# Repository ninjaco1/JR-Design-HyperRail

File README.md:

# JR-Design-HyperRail
Hyper Rail Group 7

By: Anthony Nguyen, Triet Nguyen, Ben Chan

## System Testing Videos 
Currently don't have at the moment: 
[System Testing Video]()

## Artifacts
PDF for the project summary: 
[Project Summary](https://docs.google.com/document/d/1FK-zv3ej4hmk3cCyDUM1-cvGXo1tJJXo0p-roIx5XGc/edit?usp=sharing)

Steps on how to this project runs: 
[Developer Guide](https://drive.google.com/file/d/1b8bf6LgNn7jMLtsA6zKb3VHLeMdlCe0p/view?usp=sharing)

[Design Presentation Slides](https://docs.google.com/presentation/d/1P-iVZDowQR9feOQwt1mziY3U6oYqxVLCjaJKAJ0mzws/edit?usp=sharing)

[Design Presentation Video](https://drive.google.com/file/d/1qnwT8EZ-0XLxV4VDlUW8I-kmaopJeuQv/view?usp=sharing)

[Top-Level Block Diagram](https://drive.google.com/file/d/1eomTYj-uaLoGJ_eJbNjmGpFzPQzX-4X2/view?usp=sharing)

[Time report showing time spent by each team member](https://docs.google.com/spreadsheets/d/1bjDdPKETd7_wlSsTo6gn0jvfjcJVhAvTHsii9ZCNzQg/edit?usp=sharing)

## Demo Videos with Explanation 
First change Directories so that you are in the `EdgeDetection` directory. Before running the python script change code on line 5 to 
```python 
img = cv2.imread('path/to/image.png',0)
```
. Make sure to update the file path to the image that you wish to perform edge detection on. Afterwards run `python3 edgeDetection.py`. At the end it will show the edge detection picture compared to the original one which was in gray, and a generated G-Code command text file called `gcode.txt`.
[Edge Detection Demo in Python3](https://drive.google.com/file/d/1J3HoQEe9SpAp14uiTM5HVKii-mfcHyuJ/view?usp=sharing)

To run this file make sure you are using some type of Python Interpreter otherwise it will not work. Change directory to `Parser`. To run the script run `python3 parser.py`. Then it will ask if you want to to run in manual mode or auto mode.
1. Auto Mode: provide the G-Code text file.
2. Manual Mode: Type G-Code commands one at a time

The G-Code commands must have the right parameters/arguments plus the command or it will not run. Ex: `G0 X0 Y0` would be 3 total.

1 total: G20, G21, G90, G91, M2, M6, M72, T#

3 total: G0

4 total: G1

6 total: G3

[G-Code Parser in Python3 Demo Video](https://drive.google.com/file/d/1lWumYBpXrusXX2kpaQBLoHpFK_WG9Xnz/view?usp=sharing)

[G-Code Parser in MATLAB Demo Video](https://drive.google.com/file/d/1U7hCthpk_3eQoVkrieUcnGUcYebdRAjs/view?usp=sharing)

## Picture of PCB and Toolhead 

[Google Drive folder with images of PCB layers and toolhead](https://drive.google.com/drive/folders/1xzrkDD5itXDCg26j8iZeH8htb0uEpJzJ?usp=sharing)

## Bill of Materials 

[BOM](https://drive.google.com/file/d/1bA2rW0vcZreU9mbd2lWcmnBElYSLbTTa/view?usp=sharing)

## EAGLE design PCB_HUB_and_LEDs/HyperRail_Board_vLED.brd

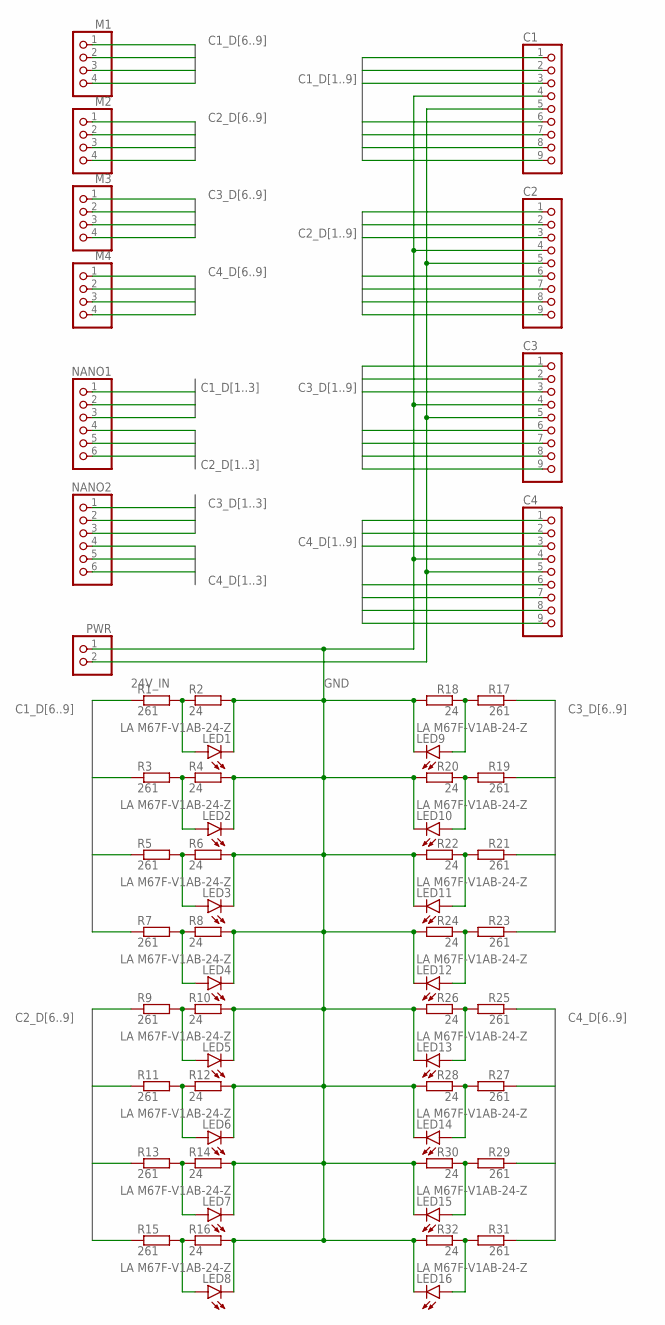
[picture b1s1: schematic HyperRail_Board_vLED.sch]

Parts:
C1, C2, C3, C4: PINHD-1X9; 1X09
LED1, LED2, LED3, LED4, LED5, LED6, LED7, LED8, LED9, LED10, LED11, LED12, LED13, LED14, LED15, LED16: LA M67F-V1AB-24-Z; PLCC2
M1, M2, M3, M4: PINHD-1X4; 1X04
NANO1, NANO2: PINHD-1X6; 1X06
PWR: PINHD-1X2; 1X02
R1, R3, R5, R7, R9, R11, R13, R15, R17, R19, R21, R23, R25, R27, R29, R31: 261; SMK
R2, R4, R6, R8, R10, R12, R14, R16, R18, R20, R22, R24, R26, R28, R30, R32: 24; SMK

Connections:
24V_IN: C1.5, C2.5, C3.5, C4.5, PWR.2
C1_D1: C1.1, NANO1.1
C1_D2: C1.2, NANO1.2
C1_D3: C1.3, NANO1.3
C1_D6: C1.6, M1.1, R1.2
C1_D7: C1.7, M1.2, R3.2
C1_D8: C1.8, M1.3, R5.2
C1_D9: C1.9, M1.4, R7.2
C2_D1: C2.1, NANO1.4
C2_D2: C2.2, NANO1.5
C2_D3: C2.3, NANO1.6
C2_D6: C2.6, M2.1, R9.2
C2_D7: C2.7, M2.2, R11.2
C2_D8: C2.8, M2.3, R13.2
C2_D9: C2.9, M2.4, R15.2
C3_D1: C3.1, NANO2.1
C3_D2: C3.2, NANO2.2
C3_D3: C3.3, NANO2.3
C3_D6: C3.6, M3.1, R17.2
C3_D7: C3.7, M3.2, R19.2
C3_D8: C3.8, M3.3, R21.2
C3_D9: C3.9, M3.4, R23.2
C4_D1: C4.1, NANO2.4
C4_D2: C4.2, NANO2.5
C4_D3: C4.3, NANO2.6
C4_D6: C4.6, M4.1, R25.2
C4_D7: C4.7, M4.2, R27.2
C4_D8: C4.8, M4.3, R29.2
C4_D9: C4.9, M4.4, R31.2
GND: C1.4, C2.4, C3.4, C4.4, LED1.C, LED2.C, LED3.C, LED4.C, LED5.C, LED6.C, LED7.C, LED8.C, LED9.C, LED10.C, LED11.C, LED12.C, LED13.C, LED14.C, LED15.C, LED16.C, PWR.1, R2.1, R4.1, R6.1, R8.1, R10.1, R12.1, R14.1, R16.1, R18.1, R20.1, R22.1, R24.1, R26.1, R28.1, R30.1, R32.1
unnamed: LED1.A, R1.1, R2.2
unnamed: LED2.A, R3.1, R4.2
unnamed: LED3.A, R5.1, R6.2
unnamed: LED4.A, R7.1, R8.2
unnamed: LED5.A, R9.1, R10.2
unnamed: LED6.A, R11.1, R12.2
unnamed: LED7.A, R13.1, R14.2
unnamed: LED8.A, R15.1, R16.2
unnamed: LED9.A, R17.1, R18.2
unnamed: LED10.A, R19.1, R20.2
unnamed: LED11.A, R21.1, R22.2
unnamed: LED12.A, R23.1, R24.2
unnamed: LED13.A, R25.1, R26.2
unnamed: LED14.A, R27.1, R28.2
unnamed: LED15.A, R29.1, R30.2
unnamed: LED16.A, R31.1, R32.2

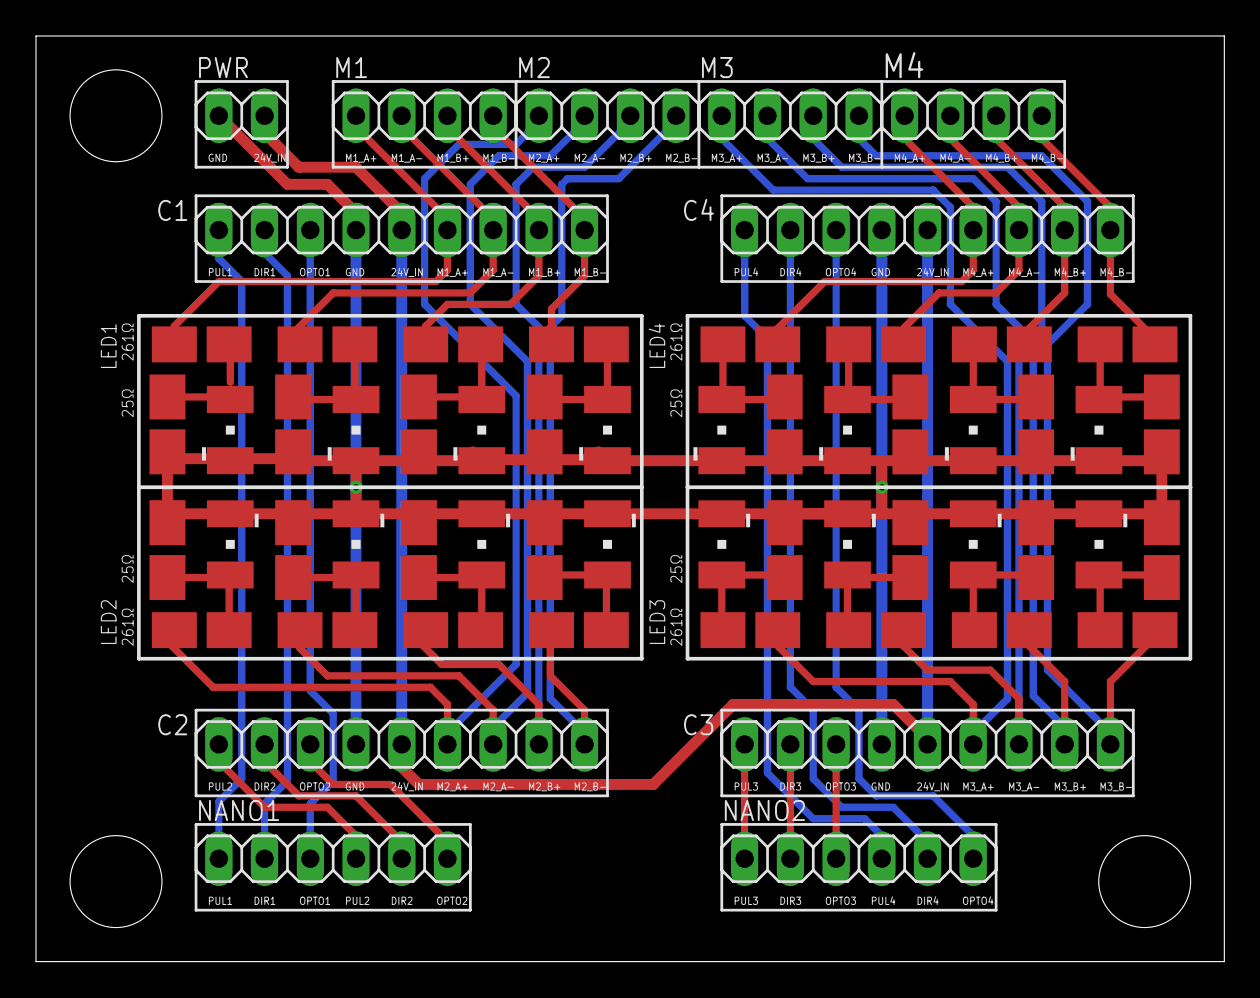
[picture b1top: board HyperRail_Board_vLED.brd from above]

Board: 2 copper layers, 66.0 x 51.4 mm, 59 parts (0 on the bottom side), 46 nets.

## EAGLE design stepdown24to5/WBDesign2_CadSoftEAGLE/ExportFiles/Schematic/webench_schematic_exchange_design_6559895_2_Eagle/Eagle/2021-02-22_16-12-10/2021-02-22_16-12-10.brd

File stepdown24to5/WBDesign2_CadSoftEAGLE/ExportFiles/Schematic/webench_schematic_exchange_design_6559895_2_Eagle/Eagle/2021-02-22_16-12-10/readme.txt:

**********************************************************
*************  Important Instructions Follow  ************
**********************************************************
 
All files exported to: Z:\\65\\59\\6559895\\2\Eagle\2021-02-22_16-12-10\2021-02-22_16-12-10.xml

**********************************************************
*****************Schematic Instructions  *******************
**********************************************************

To import your new Schematic file into Eagle:

1. Unzip the downloaded folder files to local directory and Start Eagle.
2. Select "File"->"Open"->"Schematic..." from the menu at the top of
the screen.
3. Browse to your newly exported file and select the ".sch" file extension.
4. You should now see your schamtic available in Eagle.

**********************************************************
*******************  PCB Instructions  *******************
**********************************************************

To import your new BOARD file into Eagle:

1. Unzip the downloaded folder files to local directory and Start Eagle.
2. Select "File"->"Open"->"Board..." from the menu at the top of
the screen.
3. Browse to your newly exported file and select the ".brd" file extension.
4. Planes will need to be repoured to update the polygon fills
	1. Once your board is loaded, type "ratsnest" into the command
	   line and press the Enter key.
	2. The polygons should all be filled now.
5. You should now have an image of your board available in Eagle.

**********************************************************
*******************  LIB Instructions  *******************
**********************************************************

To import your new library into Eagle:

1. Start Eagle.
2. Select "File"->"New"->"Library" from the menu.
3. In the blank library window, select "File" -> "Execute Script"
from the menu.
5. Browse to your newly exported Eagle Script file (".scr" file extension)
6. After opening the file, the script will populate the new library.
Layer 93 should NOT exist.
7. Use "File"->Save As: "AcceleratedDesigns_Lib.lbr" and to the desired
location in Eagle native format.
8. Update schematic with the imported library, Select Library and click on Update; open the library file
	and sync. each part.

For additional information, please visit this site:
http://www.accelerated-designs.com/help/Eagle_import.html

You may also find this video helpful:
http://youtu.be/5jGuWY-Yy3Q

**********************************************************
**********************************************************
**********************************************************

Component "C1608X5R1A226M080AC" renamed to "C1608X5R1A226M080AC"
Component "CRCW04022M00FKED" renamed to "CRCW04022M00FKED"
Component "CRCW0402383KFKED" renamed to "CRCW0402383KFKED"
Component "WB_GND" renamed to "WB_GND"
Component "CRCW0402100KFKED" renamed to "CRCW0402100KFKED"
Component "NPI54C100MTRF" renamed to "NPI54C100MTRF"
Component "GRM21BR71E225KA73L" renamed to "GRM21BR71E225KA73L"
Component "TPS62175DQCR" renamed to "TPS62175DQCR"
Component "WB_BATTERY" renamed to "WB_BATTERY"
Component "WB_CURRENT_LOAD" renamed to "WB_CURRENT_LOAD"
The Symbol WB_CONTINUATION was missing a RefDes attribute, a refdes was created for the symbol.
The Symbol WB_CONTINUATION was missing a Type attribute, a type was created for the symbol.
The Symbol WB_CONTINUATION was missing a Value attribute, a value was created for the symbol.
The Symbol WB_BLOCK_IO was missing a RefDes attribute, a refdes was created for the symbol.
The Symbol WB_BLOCK_IO was missing a Type attribute, a type was created for the symbol.
The Symbol WB_BLOCK_IO was missing a Value attribute, a value was created for the symbol.
The Symbol WB_PWL_VOLTAGE_SOURCE was missing a RefDes attribute, a refdes was created for the symbol.
The Symbol WB_PWL_VOLTAGE_SOURCE was missing a Type attribute, a type was created for the symbol.
The Symbol WB_PWL_VOLTAGE_SOURCE was missing a Value attribute, a value was created for the symbol.
The Symbol WB_SOURCE_RESISTOR was missing a RefDes attribute, a refdes was created for the symbol.
The Symbol WB_SOURCE_RESISTOR was missing a Type attribute, a type was created for the symbol.
The Symbol WB_SOURCE_RESISTOR was missing a Value attribute, a value was created for the symbol.
The Symbol WB_PRIM_PWL_VOLTAGE_SOURCE was missing a RefDes attribute, a refdes was created for the symbol.
The Symbol WB_PRIM_PWL_VOLTAGE_SOURCE was missing a Type attribute, a type was created for the symbol.
The Symbol WB_PRIM_PWL_VOLTAGE_SOURCE was missing a Value attribute, a value was created for the symbol.
The Symbol WB_CURRENT_PROBE was missing a RefDes attribute, a refdes was created for the symbol.
The Symbol WB_CURRENT_PROBE was missing a Type attribute, a type was created for the symbol.
The Symbol WB_CURRENT_PROBE was missing a Value attribute, a value was created for the symbol.
The Symbol WB_LOAD_RESISTOR was missing a RefDes attribute, a refdes was created for the symbol.
The Symbol WB_LOAD_RESISTOR was missing a Type attribute, a type was created for the symbol.
The Symbol WB_LOAD_RESISTOR was missing a Value attribute, a value was created for the symbol.
The Symbol WB_PRIM_STARTUP_VOLTAGE_SOURCE was missing a RefDes attribute, a refdes was created for the symbol.
The Symbol WB_PRIM_STARTUP_VOLTAGE_SOURCE was missing a Type attribute, a type was created for the symbol.
The Symbol WB_PRIM_STARTUP_VOLTAGE_SOURCE was missing a Value attribute, a value was created for the symbol.
The Symbol WB_STARTUP_VOLTAGE_SOURCE was missing a RefDes attribute, a refdes was created for the symbol.
The Symbol WB_STARTUP_VOLTAGE_SOURCE was missing a Type attribute, a type was created for the symbol.
The Symbol WB_STARTUP_VOLTAGE_SOURCE was missing a Value attribute, a value was created for the symbol.
The Symbol WB_PWL_CURRENT_LOAD was missing a RefDes attribute, a refdes was created for the symbol.
The Symbol WB_PWL_CURRENT_LOAD was missing a Type attribute, a type was created for the symbol.
The Symbol WB_PWL_CURRENT_LOAD was missing a Value attribute, a value was created for the symbol.
The Symbol WB_PRIMITIVE_BATTERY was missing a RefDes attribute, a refdes was created for the symbol.
The Symbol WB_PRIMITIVE_BATTERY was missing a Type attribute, a type was created for the symbol.
The Symbol WB_PRIMITIVE_BATTERY was missing a Value attribute, a value was created for the symbol.
The Symbol WB_VOLTAGE_PROBE was missing a RefDes attribute, a refdes was created for the symbol.
The Symbol WB_VOLTAGE_PROBE was missing a Type attribute, a type was created for the symbol.
The Symbol WB_VOLTAGE_PROBE was missing a Value attribute, a value was created for the symbol.
The Symbol WB_TPS62175DQC was missing a RefDes attribute, a refdes was created for the symbol.
The Symbol WB_TPS62175DQC was missing a Type attribute, a type was created for the symbol.
The Symbol WB_TPS62175DQC was missing a Value attribute, a value was created for the symbol.

Ultra Librarian Gold 8.1.204 Process Report

Message - Padstack "RX26Y38D0T" Shape(4) is a CIRCLE with no diameter.
Message - Padstack "RX22Y24D0T" Shape(4) is a CIRCLE with no diameter.
Message - Padstack "RX84p5Y217D0T" Shape(4) is a CIRCLE with no diameter.
Message - Padstack "RX44Y57D0T" Shape(4) is a CIRCLE with no diameter.
Message - Padstack "R10100200000200A" Shape(4) is a CIRCLE with no diameter.
Message - Padstack "R10330940000217A" Shape(4) is a CIRCLE with no diameter.
Message - Pattern "IND_NPI54C", entity (115-Line) is a LINE with matching start and end points.
Message - Pattern "IND_NPI54C", entity (117-Line) is a LINE with matching start and end points.
Message - Pattern "IND_NPI54C", entity (119-Line) is a LINE with matching start and end points.
Message - Pattern "IND_NPI54C", entity (121-Line) is a LINE with matching start and end points.
Message - Symbol "WB_CAPACITOR" has as multiple attributes named "TYPE".
One of the attributes was renamed to "TYPE_2".
Message - Component "C1608X5R1A226M080AC" attribute "Datasheet URL" references text style "" that is not in the database.
The default pattern text style "H50s3" was substituted.
Message - Component "C1608X5R1A226M080AC" attribute "Cap" references text style "" that is not in the database.
The default pattern text style "H50s3" was substituted.
Message - Component "C1608X5R1A226M080AC" attribute "ESR" references text style "" that is not in the database.
The default pattern text style "H50s3" was substituted.
Message - Component "C1608X5R1A226M080AC" attribute "IRMS" references text style "" that is not in the database.
The default pattern text style "H50s3" was substituted.
Message - Component "C1608X5R1A226M080AC" attribute "VDC" references text style "" that is not in the database.
The default pattern text style "H50s3" was substituted.
Message - Component "CRCW04022M00FKED" attribute "Resistance" references text style "" that is not in the database.
The default pattern text style "H50s3" was substituted.
Message - Component "CRCW04022M00FKED" attribute "Power" references text style "" that is not in the database.
The default pattern text style "H50s3" was substituted.
Message - Component "CRCW04022M00FKED" attribute "Tolerance" references text style "" that is not in the database.
The default pattern text style "H50s3" was substituted.
Message - Component "CRCW0402383KFKED" attribute "Resistance" references text style "" that is not in the database.
The default pattern text style "H50s3" was substituted.
Message - Component "CRCW0402383KFKED" attribute "Power" references text style "" that is not in the database.
The default pattern text style "H50s3" was substituted.
Message - Component "CRCW0402383KFKED" attribute "Tolerance" references text style "" that is not in the database.
The default pattern text style "H50s3" was substituted.
Message - Component "CRCW0402100KFKED" attribute "Resistance" references text style "" that is not in the database.
The default pattern text style "H50s3" was substituted.
Message - Component "CRCW0402100KFKED" attribute "Power" references text style "" that is not in the database.
The default pattern text style "H50s3" was substituted.
Message - Component "CRCW0402100KFKED" attribute "Tolerance" references text style "" that is not in the database.
The default pattern text style "H50s3" was substituted.
Message - Component "NPI54C100MTRF" attribute "L" references text style "" that is not in the database.
The default pattern text style "H50s3" was substituted.
Message - Component "NPI54C100MTRF" attribute "DCR" references text style "" that is not in the database.
The default pattern text style "H50s3" was substituted.
Message - Component "NPI54C100MTRF" attribute "IDC" references text style "" that is not in the database.
The default pattern text style "H50s3" was substituted.
Message - Component "GRM21BR71E225KA73L" attribute "Cap" references text style "" that is not in the database.
The default pattern text style "H50s3" was substituted.
Message - Component "GRM21BR71E225KA73L" attribute "ESR" references text style "" that is not in the database.
The default pattern text style "H50s3" was substituted.
Message - Component "GRM21BR71E225KA73L" attribute "IRMS" references text style "" that is not in the database.
The default pattern text style "H50s3" was substituted.
Message - Component "GRM21BR71E225KA73L" attribute "VDC" references text style "" that is not in the database.
The default pattern text style "H50s3" was substituted.

TextStyle count:  24
Padstack count:   6
Pattern count:    5
Symbol count:     20
Component count:  10

Export

Footprint "WB_GND" has no layer data mapped and will be skipped.
Component "WB_GND" requires footprint "WB_GND" and will be skipped.
Footprint "WB_BATTERY" has no layer data mapped and will be skipped.
Component "WB_BATTERY" requires footprint "WB_BATTERY" and will be skipped.
Footprint "WB_CURRENT_LOAD" has no layer data mapped and will be skipped.
Component "WB_CURRENT_LOAD" requires footprint "WB_CURRENT_LOAD" and will be skipped.

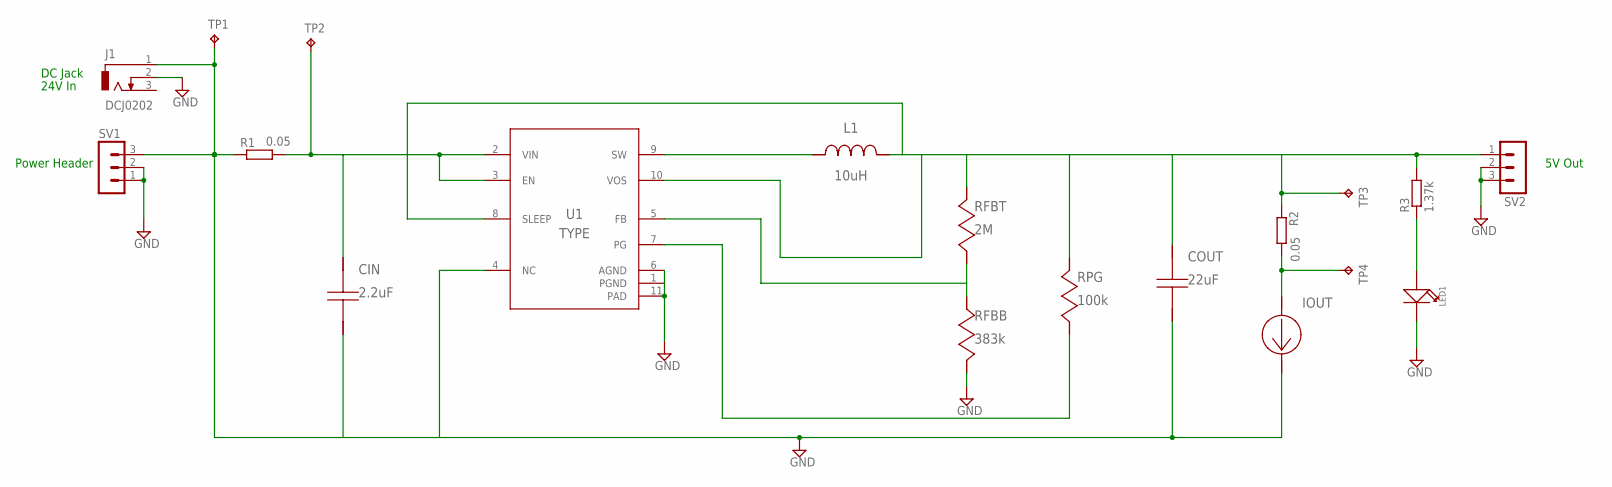
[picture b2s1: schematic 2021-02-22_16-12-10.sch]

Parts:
CIN: 2.2uF; 0805
COUT: 22uF; 0603
IOUT: WB_CURRENT_LOAD
J1: DCJ0202
L1: 10uH; IND_NPI54C
LED1: LED-THT
R1, R2: 0.05; R0603
R3: 1.37k; R0603
RFBB: 383k; 0402
RFBT: 2M; 0402
RPG: 100k; 0402
SV1, SV2: MA03-1
TP1, TP2, TP3, TP4: TPPAD1-20; P1-20
U1: TPS62175DQCR; DQC0010A

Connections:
1: RPG.2, U1.7 (PG)
2: COUT.1, RFBT.1, RPG.1, U1.8 (SLEEP), U1.10 (VOS)
3: L1.1, U1.9 (SW)
4: RFBB.2, RFBT.2, U1.5 (FB)
5: CIN.2, U1.4 (NC)
GND: COUT.2, IOUT.2 (-), J1.1, J1.2, LED1.1 (MINUS), R1.1, RFBB.1, SV1.1, SV1.2, SV1.3, SV2.2, SV2.3, TP1.TP, U1.1 (PGND), U1.6 (AGND), U1.11 (PAD)
unnamed: CIN.1, R1.2, TP2.TP, U1.2 (VIN), U1.3 (EN)
unnamed: IOUT.1 (+), R2.2, TP4.TP
unnamed: L1.2, R2.1, R3.2, SV2.1, TP3.TP
unnamed: LED1.2 (PLUS), R3.1

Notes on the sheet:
Power Header
DC Jack
5V Out
24V In

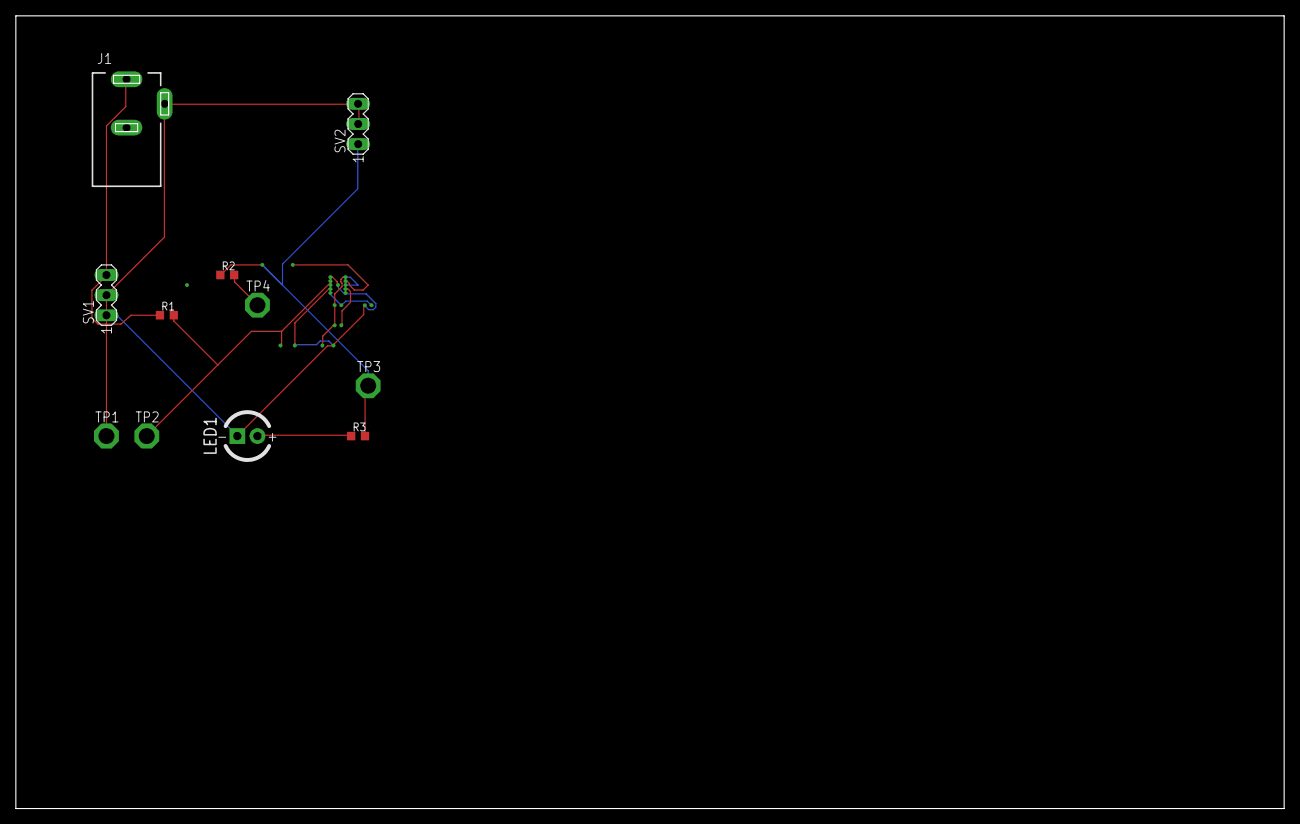
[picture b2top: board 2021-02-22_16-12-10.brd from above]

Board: 2 copper layers, 160.0 x 100.0 mm, 19 parts (1 on the bottom side), 10 nets.

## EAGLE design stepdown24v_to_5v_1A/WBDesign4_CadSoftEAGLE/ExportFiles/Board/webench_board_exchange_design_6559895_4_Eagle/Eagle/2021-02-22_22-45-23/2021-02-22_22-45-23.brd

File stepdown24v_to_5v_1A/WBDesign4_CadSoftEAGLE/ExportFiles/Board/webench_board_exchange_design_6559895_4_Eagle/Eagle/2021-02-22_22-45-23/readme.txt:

**********************************************************
*************  Important Instructions Follow  ************
**********************************************************
 
All files exported to: Z:\\65\\59\\6559895\\4\Eagle\2021-02-22_22-45-23\2021-02-22_22-45-23.xml

**********************************************************
*****************Schematic Instructions  *******************
**********************************************************

To import your new Schematic file into Eagle:

1. Unzip the downloaded folder files to local directory and Start Eagle.
2. Select "File"->"Open"->"Schematic..." from the menu at the top of
the screen.
3. Browse to your newly exported file and select the ".sch" file extension.
4. You should now see your schamtic available in Eagle.

**********************************************************
*******************  PCB Instructions  *******************
**********************************************************

To import your new BOARD file into Eagle:

1. Unzip the downloaded folder files to local directory and Start Eagle.
2. Select "File"->"Open"->"Board..." from the menu at the top of
the screen.
3. Browse to your newly exported file and select the ".brd" file extension.
4. Planes will need to be repoured to update the polygon fills
	1. Once your board is loaded, type "ratsnest" into the command
	   line and press the Enter key.
	2. The polygons should all be filled now.
5. You should now have an image of your board available in Eagle.

**********************************************************
*******************  LIB Instructions  *******************
**********************************************************

To import your new library into Eagle:

1. Start Eagle.
2. Select "File"->"New"->"Library" from the menu.
3. In the blank library window, select "File" -> "Execute Script"
from the menu.
5. Browse to your newly exported Eagle Script file (".scr" file extension)
6. After opening the file, the script will populate the new library.
Layer 93 should NOT exist.
7. Use "File"->Save As: "AcceleratedDesigns_Lib.lbr" and to the desired
location in Eagle native format.
8. Update schematic with the imported library, Select Library and click on Update; open the library file
	and sync. each part.

For additional information, please visit this site:
http://www.accelerated-designs.com/help/Eagle_import.html

You may also find this video helpful:
http://youtu.be/5jGuWY-Yy3Q

**********************************************************
**********************************************************
**********************************************************

Component "NPI105C220MTRF" renamed to "NPI105C220MTRF"
Component "GRM31CR71H475KA12L" renamed to "GRM31CR71H475KA12L"
Component "C3216X6S1V106K160AC" renamed to "C3216X6S1V106K160AC"
Component "CRCW040220K0FKED" renamed to "CRCW040220K0FKED"
Component "RT0805BRD07111KL" renamed to "RT0805BRD07111KL"
Component "LMR14010ADDCR" renamed to "LMR14010ADDCR"
Component "SS24FL" renamed to "SS24FL"
Component "C0805C104M5RACTU" renamed to "C0805C104M5RACTU"
Component "TP-1502" renamed to "TP-1502"

Ultra Librarian Gold 8.1.204 Process Report

Message - Padstack "RX148Y374D0T" Shape(4) is a CIRCLE with no diameter.
Message - Padstack "RX44Y71D0T" Shape(4) is a CIRCLE with no diameter.
Message - Padstack "RX22Y24D0T" Shape(4) is a CIRCLE with no diameter.
Message - Padstack "RX44Y57D0T" Shape(4) is a CIRCLE with no diameter.
Message - Padstack "R10240390000200A" Shape(4) is a CIRCLE with no diameter.
Message - Padstack "R10260470000200A" Shape(4) is a CIRCLE with no diameter.
Message - Padstack "R10220310000200A" Shape(4) is a CIRCLE with no diameter.
Message - Padstack "R10470470000202A" Shape(4) is a CIRCLE with no diameter.
Message - Pattern "IND_NPI105C", entity (115-Line) is a LINE with matching start and end points.
Message - Pattern "IND_NPI105C", entity (117-Line) is a LINE with matching start and end points.
Message - Pattern "IND_NPI105C", entity (119-Line) is a LINE with matching start and end points.
Message - Pattern "IND_NPI105C", entity (121-Line) is a LINE with matching start and end points.
Message - Component "NPI105C220MTRF" attribute "L" references text style "" that is not in the database.
The default pattern text style "H50s3" was substituted.
Message - Component "NPI105C220MTRF" attribute "DCR" references text style "" that is not in the database.
The default pattern text style "H50s3" was substituted.
Message - Component "NPI105C220MTRF" attribute "IDC" references text style "" that is not in the database.
The default pattern text style "H50s3" was substituted.
Message - Component "GRM31CR71H475KA12L" attribute "Cap" references text style "" that is not in the database.
The default pattern text style "H50s3" was substituted.
Message - Component "GRM31CR71H475KA12L" attribute "ESR" references text style "" that is not in the database.
The default pattern text style "H50s3" was substituted.
Message - Component "GRM31CR71H475KA12L" attribute "IRMS" references text style "" that is not in the database.
The default pattern text style "H50s3" was substituted.
Message - Component "GRM31CR71H475KA12L" attribute "VDC" references text style "" that is not in the database.
The default pattern text style "H50s3" was substituted.
Message - Component "C3216X6S1V106K160AC" attribute "Datasheet URL" references text style "" that is not in the database.
The default pattern text style "H50s3" was substituted.
Message - Component "C3216X6S1V106K160AC" attribute "Cap" references text style "" that is not in the database.
The default pattern text style "H50s3" was substituted.
Message - Component "C3216X6S1V106K160AC" attribute "ESR" references text style "" that is not in the database.
The default pattern text style "H50s3" was substituted.
Message - Component "C3216X6S1V106K160AC" attribute "IRMS" references text style "" that is not in the database.
The default pattern text style "H50s3" was substituted.
Message - Component "C3216X6S1V106K160AC" attribute "VDC" references text style "" that is not in the database.
The default pattern text style "H50s3" was substituted.
Message - Component "CRCW040220K0FKED" attribute "Resistance" references text style "" that is not in the database.
The default pattern text style "H50s3" was substituted.
Message - Component "CRCW040220K0FKED" attribute "Power" references text style "" that is not in the database.
The default pattern text style "H50s3" was substituted.
Message - Component "CRCW040220K0FKED" attribute "Tolerance" references text style "" that is not in the database.
The default pattern text style "H50s3" was substituted.
Message - Component "RT0805BRD07111KL" attribute "Resistance" references text style "" that is not in the database.
The default pattern text style "H50s3" was substituted.
Message - Component "RT0805BRD07111KL" attribute "Power" references text style "" that is not in the database.
The default pattern text style "H50s3" was substituted.
Message - Component "RT0805BRD07111KL" attribute "Tolerance" references text style "" that is not in the database.
The default pattern text style "H50s3" was substituted.
Message - Component "SS24FL" attribute "Datasheet URL" references text style "" that is not in the database.
The default pattern text style "H50s3" was substituted.
Message - Component "SS24FL" attribute "Io" references text style "" that is not in the database.
The default pattern text style "H50s3" was substituted.
Message - Component "SS24FL" attribute "VRRM" references text style "" that is not in the database.
The default pattern text style "H50s3" was substituted.
Message - Component "SS24FL" attribute "VFatIo" references text style "" that is not in the database.
The default pattern text style "H50s3" was substituted.
Message - Component "C0805C104M5RACTU" attribute "Cap" references text style "" that is not in the database.
The default pattern text style "H50s3" was substituted.
Message - Component "C0805C104M5RACTU" attribute "ESR" references text style "" that is not in the database.
The default pattern text style "H50s3" was substituted.
Message - Component "C0805C104M5RACTU" attribute "IRMS" references text style "" that is not in the database.
The default pattern text style "H50s3" was substituted.
Message - Component "C0805C104M5RACTU" attribute "VDC" references text style "" that is not in the database.
The default pattern text style "H50s3" was substituted.

TextStyle count:  25
Padstack count:   11
Pattern count:    10
Symbol count:     6
Component count:  9

Export

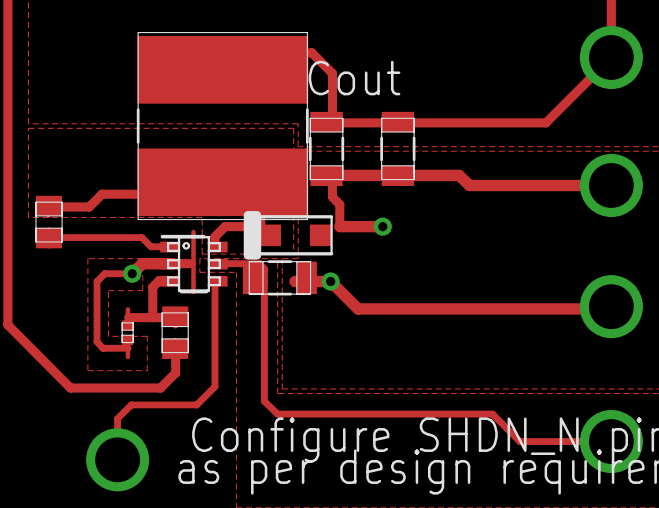
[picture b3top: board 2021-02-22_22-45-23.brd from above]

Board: 4 copper layers, 14 parts (0 on the bottom side), 7 nets.

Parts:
Cboot: 0805
Cin: 1206
Cout_1, Cout_2: 1206_180
D1: SOD-123F
GND, GND1: TP-1502
L1: IND_NPI105C
Rfbb: 0402
Rfbt: 0805
SHDN_N: TP-1502
U1: DDC0006A_N
VIN: TP-1502
VOUT: TP-1502

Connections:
0: Cin.2, Cout_1.2, Cout_2.2, D1.2, GND.1, GND1.1, Rfbb.2, U1.2
1: Cboot.1, U1.1
2: Rfbb.1, Rfbt.2, U1.3
5: Cout_1.1, Cout_2.1, L1.2, Rfbt.1, VOUT.1
6: Cboot.2, D1.1, L1.1, U1.6
12: Cin.1, U1.5, VIN.1
14: SHDN_N.1, U1.4

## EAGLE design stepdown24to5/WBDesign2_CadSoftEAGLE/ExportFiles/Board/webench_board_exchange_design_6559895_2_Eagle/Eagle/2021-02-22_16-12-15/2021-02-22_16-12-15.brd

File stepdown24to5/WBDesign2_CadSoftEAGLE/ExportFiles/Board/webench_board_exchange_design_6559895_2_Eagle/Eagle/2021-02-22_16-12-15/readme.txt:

**********************************************************
*************  Important Instructions Follow  ************
**********************************************************
 
All files exported to: Z:\\65\\59\\6559895\\2\Eagle\2021-02-22_16-12-15\2021-02-22_16-12-15.xml

**********************************************************
*****************Schematic Instructions  *******************
**********************************************************

To import your new Schematic file into Eagle:

1. Unzip the downloaded folder files to local directory and Start Eagle.
2. Select "File"->"Open"->"Schematic..." from the menu at the top of
the screen.
3. Browse to your newly exported file and select the ".sch" file extension.
4. You should now see your schamtic available in Eagle.

**********************************************************
*******************  PCB Instructions  *******************
**********************************************************

To import your new BOARD file into Eagle:

1. Unzip the downloaded folder files to local directory and Start Eagle.
2. Select "File"->"Open"->"Board..." from the menu at the top of
the screen.
3. Browse to your newly exported file and select the ".brd" file extension.
4. Planes will need to be repoured to update the polygon fills
	1. Once your board is loaded, type "ratsnest" into the command
	   line and press the Enter key.
	2. The polygons should all be filled now.
5. You should now have an image of your board available in Eagle.

**********************************************************
*******************  LIB Instructions  *******************
**********************************************************

To import your new library into Eagle:

1. Start Eagle.
2. Select "File"->"New"->"Library" from the menu.
3. In the blank library window, select "File" -> "Execute Script"
from the menu.
5. Browse to your newly exported Eagle Script file (".scr" file extension)
6. After opening the file, the script will populate the new library.
Layer 93 should NOT exist.
7. Use "File"->Save As: "AcceleratedDesigns_Lib.lbr" and to the desired
location in Eagle native format.
8. Update schematic with the imported library, Select Library and click on Update; open the library file
	and sync. each part.

For additional information, please visit this site:
http://www.accelerated-designs.com/help/Eagle_import.html

You may also find this video helpful:
http://youtu.be/5jGuWY-Yy3Q

**********************************************************
**********************************************************
**********************************************************

Component "GRM21BR71E225KA73L" renamed to "GRM21BR71E225KA73L"
Component "TPS62175DQCR" renamed to "TPS62175DQCR"
Component "CRCW0402100KFKED" renamed to "CRCW0402100KFKED"
Component "CRCW0402383KFKED" renamed to "CRCW0402383KFKED"
Component "CRCW04022M00FKED" renamed to "CRCW04022M00FKED"
Component "NPI54C100MTRF" renamed to "NPI54C100MTRF"
Component "C1608X5R1A226M080AC" renamed to "C1608X5R1A226M080AC"
Component "TP-1502" renamed to "TP-1502"

Ultra Librarian Gold 8.1.204 Process Report

Message - Padstack "R10100200000200A" Shape(4) is a CIRCLE with no diameter.
Message - Padstack "R10330940000217A" Shape(4) is a CIRCLE with no diameter.
Message - Padstack "RX22Y24D0T" Shape(4) is a CIRCLE with no diameter.
Message - Padstack "RX84p5Y217D0T" Shape(4) is a CIRCLE with no diameter.
Message - Padstack "RX26Y38D0T" Shape(4) is a CIRCLE with no diameter.
Message - Padstack "RX44Y57D0T" Shape(4) is a CIRCLE with no diameter.
Message - Pattern "IND_NPI54C", entity (115-Line) is a LINE with matching start and end points.
Message - Pattern "IND_NPI54C", entity (117-Line) is a LINE with matching start and end points.
Message - Pattern "IND_NPI54C", entity (119-Line) is a LINE with matching start and end points.
Message - Pattern "IND_NPI54C", entity (121-Line) is a LINE with matching start and end points.
Message - Symbol "WB_CAPACITOR" has as multiple attributes named "TYPE".
One of the attributes was renamed to "TYPE_2".
Message - Component "GRM21BR71E225KA73L" attribute "Cap" references text style "" that is not in the database.
The default pattern text style "H50s3" was substituted.
Message - Component "GRM21BR71E225KA73L" attribute "ESR" references text style "" that is not in the database.
The default pattern text style "H50s3" was substituted.
Message - Component "GRM21BR71E225KA73L" attribute "IRMS" references text style "" that is not in the database.
The default pattern text style "H50s3" was substituted.
Message - Component "GRM21BR71E225KA73L" attribute "VDC" references text style "" that is not in the database.
The default pattern text style "H50s3" was substituted.
Message - Component "CRCW0402100KFKED" attribute "Resistance" references text style "" that is not in the database.
The default pattern text style "H50s3" was substituted.
Message - Component "CRCW0402100KFKED" attribute "Power" references text style "" that is not in the database.
The default pattern text style "H50s3" was substituted.
Message - Component "CRCW0402100KFKED" attribute "Tolerance" references text style "" that is not in the database.
The default pattern text style "H50s3" was substituted.
Message - Component "CRCW0402383KFKED" attribute "Resistance" references text style "" that is not in the database.
The default pattern text style "H50s3" was substituted.
Message - Component "CRCW0402383KFKED" attribute "Power" references text style "" that is not in the database.
The default pattern text style "H50s3" was substituted.
Message - Component "CRCW0402383KFKED" attribute "Tolerance" references text style "" that is not in the database.
The default pattern text style "H50s3" was substituted.
Message - Component "CRCW04022M00FKED" attribute "Resistance" references text style "" that is not in the database.
The default pattern text style "H50s3" was substituted.
Message - Component "CRCW04022M00FKED" attribute "Power" references text style "" that is not in the database.
The default pattern text style "H50s3" was substituted.
Message - Component "CRCW04022M00FKED" attribute "Tolerance" references text style "" that is not in the database.
The default pattern text style "H50s3" was substituted.
Message - Component "NPI54C100MTRF" attribute "L" references text style "" that is not in the database.
The default pattern text style "H50s3" was substituted.
Message - Component "NPI54C100MTRF" attribute "DCR" references text style "" that is not in the database.
The default pattern text style "H50s3" was substituted.
Message - Component "NPI54C100MTRF" attribute "IDC" references text style "" that is not in the database.
The default pattern text style "H50s3" was substituted.
Message - Component "C1608X5R1A226M080AC" attribute "Datasheet URL" references text style "" that is not in the database.
The default pattern text style "H50s3" was substituted.
Message - Component "C1608X5R1A226M080AC" attribute "Cap" references text style "" that is not in the database.
The default pattern text style "H50s3" was substituted.
Message - Component "C1608X5R1A226M080AC" attribute "ESR" references text style "" that is not in the database.
The default pattern text style "H50s3" was substituted.
Message - Component "C1608X5R1A226M080AC" attribute "IRMS" references text style "" that is not in the database.
The default pattern text style "H50s3" was substituted.
Message - Component "C1608X5R1A226M080AC" attribute "VDC" references text style "" that is not in the database.
The default pattern text style "H50s3" was substituted.

TextStyle count:  24
Padstack count:   10
Pattern count:    6
Symbol count:     5
Component count:  8

Export

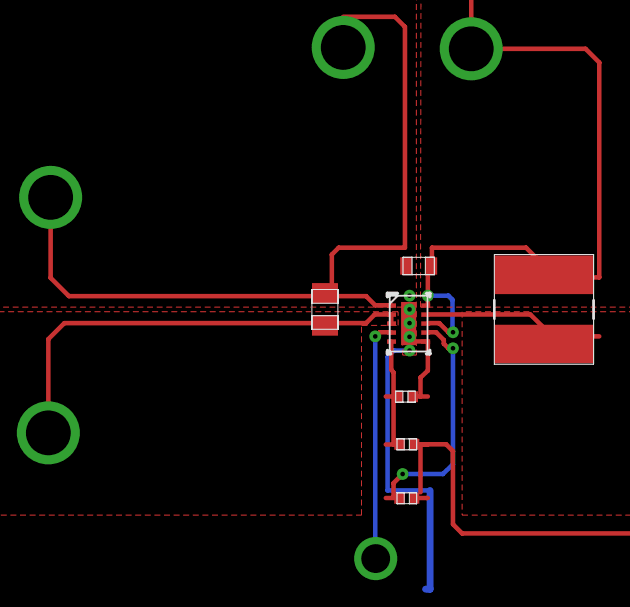
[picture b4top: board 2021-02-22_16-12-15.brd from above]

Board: 4 copper layers, 12 parts (0 on the bottom side), 6 nets.

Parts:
Cin: 0805
Cout: 0603
GND, GND1: TP-1502
L1: IND_NPI54C
Rfbb: 0402
Rfbt: 0402
Rpg: 0402
TP_NC4: TP-1502
U1: DQC0010A
VIN: TP-1502
VOUT: TP-1502

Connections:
0: Cin.2, Cout.2, GND.1, GND1.1, Rfbb.1, TP_NC4.1, U1.1, U1.4, U1.6, U1.11
1: Rpg.2, U1.7
2: Cout.1, L1.2, Rfbt.1, Rpg.1, U1.8, U1.10, VOUT.1
3: L1.1, U1.9
4: Rfbb.2, Rfbt.2, U1.5
5: Cin.1, U1.2, U1.3, VIN.1

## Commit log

2021-01-20 exit done
2021-01-24 Moved files into /Parser
2021-01-24 draw
2021-01-25 testing
2021-01-28 Parser code
2021-02-15 matlab
2021-02-23 power supply 24V to 5V
2021-02-23 changed to 1A
2021-02-24 Create info
2021-02-24 Rename info to info.md
2021-02-24 new parts in schematic
2021-02-25 BOM for stepdown
2021-02-27 Part changes for 3D printing
    Fixed broken geometry and odd dimensions (ie 0.488 -> 0.50).
    Added lightening holes to Gantry Mount.
2021-02-27 Drawings, parts list, and assem files
2021-02-27 Updated stock parts
    Added dowel, collar, bearings, and servo parts to /stock directory
2021-03-03 update readme for parser
2021-03-05 edge_detection
2021-03-05 Updated MATLAB
2021-03-06 update edge detection python
2021-03-16 Update README.md
    fixed typo, reworded a couple sections

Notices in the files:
PCB_HUB_and_LEDs/HyperRail_Board_vLED.brd:
© Ben Chan, 2021
